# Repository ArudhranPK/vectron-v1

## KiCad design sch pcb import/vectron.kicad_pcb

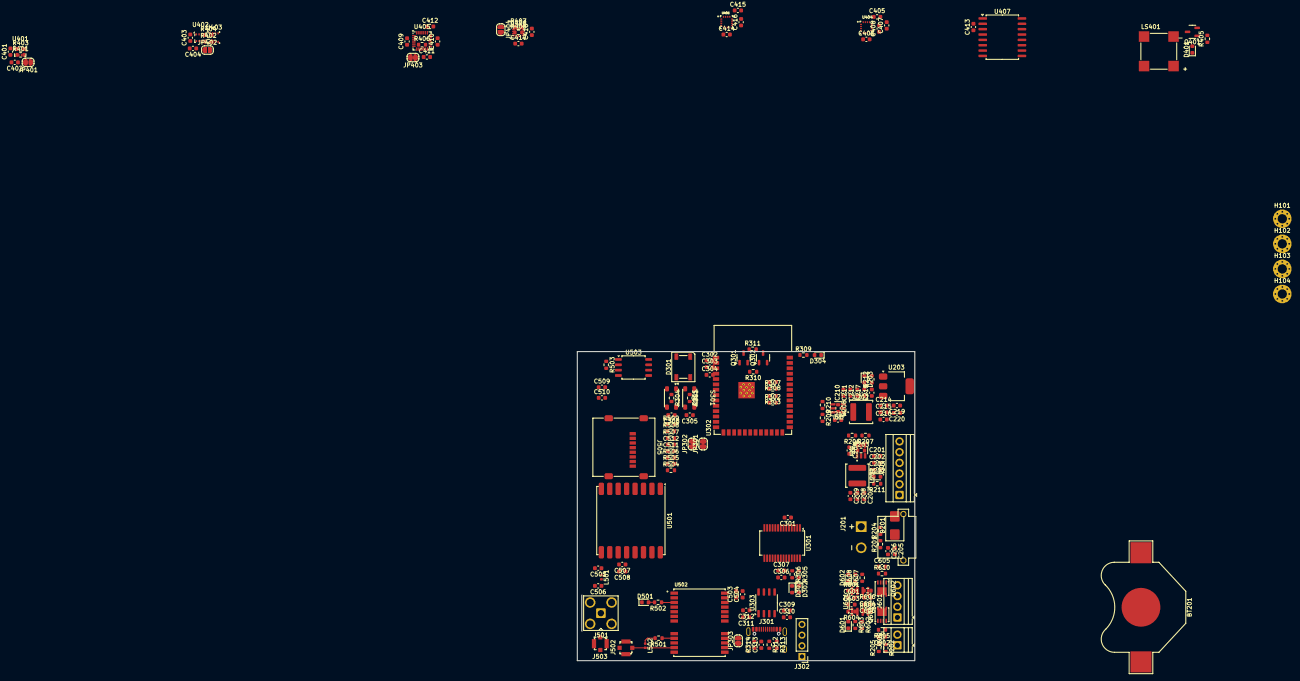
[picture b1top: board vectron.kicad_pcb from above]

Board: 4 copper layers, 80.1 x 73.3 mm, 183 parts (0 on the bottom side), 100 nets.

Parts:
BT201: BATT_3V; BatteryHolder_Multicomp_BC-2001_1x2032_modified
C201, C204, C206, C209, C210, C213, C216, C217, C220, C301, C304, C305, C307, C308, C310, C312, C313, C401, C402, C403, C404, C405, C406, C409, C410, C411, C413, C414, C415, C417, C418, C601, C602, C603, C604, C605, C606: 100nf; C_0603_1608Metric
C202, C203, C205, C211, C212, C218, C219, C302, C303, C306, C309, C311, C416, C503, C504, C507, C508, C509, C510, C511, C512: 10uf; C_0603_1608Metric
C207, C208, C214, C215: 22uf; C_0603_1608Metric
C407: 4u7f; C_0603_1608Metric
C408: 220nf; C_0603_1608Metric
C412: 2n2f; C_0603_1608Metric
C505, C506: 3pf; C_0603_1608Metric
D201: SS24-SMB; D_SMB
D202, D203: white; LED_0603_1608Metric
D301: WS2812B; LED_WS2812B_PLCC4_5.0x5.0mm_P3.2mm
D302, D303, D304: blue; LED_0603_1608Metric
D401: SS24-SMB; LED_0603_1608Metric
D501: green; LED_0603_1608Metric
D601, D602: red; LED_0603_1608Metric
H101, H102, H103, H104: MountingHole_Pad; MountingHole_2.2mm_M2_Pad_Via
J201: XT30PW-M; AMASS_XT30PW-M
J202: Screw_01x02; TerminalBlock_Xinya_XY308-2.54-2P_1x02_P2.54mm_Horizontal
J301: USB_C_Receptacle_USB2.0_16P; USB_C_Receptacle_GCT_USB4105-xx-A_16P_TopMnt_Horizontal
J302: Conn_01x04_Pin; PinHeader_1x04_P2.54mm_Vertical
J501: Conn_Coaxial; SMA_Amphenol_901-143_Horizontal
J502, J503: 0734120114; Molex_734120114_UMC_RF_CONN_Vertical
J504: Screw_Terminal_01x06; TerminalBlock_Xinya_XY308-2.54-6P_1x06_P2.54mm_Horizontal
J505: Micro_SD_Card; microSD_HC_Molex_47219-2001
J601: Screw_Terminal_01x04; TerminalBlock_Xinya_XY308-2.54-4P_1x04_P2.54mm_Horizontal
JP301, JP302, JP303, JP401, JP402, JP403, JP404: Jumper; SolderJumper-2_P1.3mm_Open_RoundedPad1.0x1.5mm
L201, L202: SWPA5040S3R3NT 3u3h; L_Sunlord_SWPA5040S
L501: 10nh; L_0402_1005Metric
L502: 27nh; L_0402_1005Metric
LS401: CMT-8530S-SMT; CUI_CMT-8530S-SMT
Q301, Q302, Q401: SS8050; SOT-23-3
Q601, Q602: SISA12ADN; Vishay_PowerPAK_1212-8_Single
R201, R202: 18k; R_0603_1608Metric
R203, R208, R302, R303: 4k7; R_0603_1608Metric
R204, R205, R207, R210, R301, R304, R310, R311, R401, R402, R403, R404, R406, R407, R408, R503, R504, R505, R506, R507, R508, R509: 10k; R_0603_1608Metric
R206: 54k9; R_0603_1608Metric
R209: 33k2; R_0603_1608Metric
R211, R212, R305, R306, R309, R405, R502, R601, R602, R603, R604, R605, R606, R607, R608, R609, R610: 1k; R_0603_1608Metric
R307, R308: 2k2; R_0603_1608Metric
R312, R313: 5k1; R_0603_1608Metric
R314: 100k; R_0603_1608Metric
R501: 10; R_0603_1608Metric
S301, S302: TK-066S; tact switch 3.4x2.5mm
U201, U202: TPS563201DDCR; SOT95P280X110-6N
U203: AMS1117-3.3; SOT-223-3_TabPin2
U301: FT232RL; SSOP-28_5.3x10.2mm_P0.65mm
U302: ESP32-S3-WROOM-1
U303: USB6B1RL; SO-8_3.9x4.9mm_P1.27mm
U401, U402: BMP280; Bosch_LGA-8_2x2.5mm_P0.65mm_ClockwisePinNumbering
U403: BME280; Bosch_LGA-8_2.5x2.5mm_P0.65mm_ClockwisePinNumbering
U404: HMC5883L-TR; XDCR_HMC5883L-TR
U405: MPU-6050; InvenSense_QFN-24_4x4mm_P0.5mm
U406: MMC5983MA; PQFN50P300X300X100-16N
U407: DS3231M; SOIC-16W_7.5x10.3mm_P1.27mm
U408: LSM6DSL; LGA-14_3x2.5mm_P0.5mm_LayoutBorder3x4y
U501: RFM98W-433S2; HOPERF_RFM9XW_SMD
U502: NEO-6M-GPS; XCVR_NEO-6M-GPS
U503: W25Q128JVS; SOIC-8_5.3x5.3mm_P1.27mm
U601: LM358; SOIC-8_3.9x4.9mm_P1.27mm

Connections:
+3V3: C214.1, C215.1, C216.1, C219.1, C220.1, C302.1, C303.1, C304.1, C401.1, C402.1, C403.1, C404.1, C405.1, C406.1, C409.1, C410.1, C413.2, C414.1, C415.1, C417.1, C418.1, C503.1, C504.1, C507.1, C508.1, C509.1, C510.1, C511.1, C512.1, D301.1 (VDD), D401.1 (K), J505.4 (VDD), JP401.2 (B), JP402.2 (B), JP403.2 (B), JP404.2 (B), L202.2, LS401.P, R209.2, R212.2, R301.1, R302.1, R303.2, R304.1, R307.1, R308.2, R401.2, R402.2, R407.2, R503.2, R504.2, R505.2, R506.2, R507.2, R508.2, R509.2, R601.2, R606.2, U203.2 (VO), U302.2 (3V3), U401.6 (VDDIO), U401.8 (VDD), U402.6 (VDDIO), U402.8 (VDD), U403.6 (VDDIO), U403.8 (VDD), U404.2 (VDD), U404.4 (S1), U404.13 (VDDIO), U405.8 (VLOGIC), U405.13 (VDD), U406.2 (VDD), U406.4 (~SPI_CS), U406.13 (VDDIO), U407.2 (VCC), U408.5 (VDDIO), U408.8 (VDD), U501.13 (3.3V), U502.23 (VCC), U503.3 (~WP/IO_{2}), U503.7 (~HOLD/~RESET/IO_{3}), U503.8 (VCC), U601.8 (V+)
+5V: C207.1, C208.1, C209.1, J504.1, J504.4, L201.2, R206.2, R211.2
+BATT: C201.1, C202.1, C203.1, C205.1, C206.1, C210.1, C211.1, C212.1, C217.1, C218.1, D201.1 (K), J201.P, R201.1, R203.1, R208.1, U201.3 (VIN), U202.3 (VIN), U203.3 (VI)
+PYRO_BAT: J202.2, J601.1, J601.3, R202.1
/ESP32/CC1: J301.A5 (CC1), R312.1
/ESP32/CC2: J301.B5 (CC2), R313.1
/ESP32/DTR_BASE: Q301.1 (B), R310.2
/ESP32/RTS_BASE: Q302.1 (B), R311.2
/ESP32/RXL: R306.1, U301.22 (CBUS1)
/ESP32/RXLED: D303.1 (K), R306.2
/ESP32/TXL: R305.1, U301.23 (CBUS0)
/ESP32/TXLED: D302.1 (K), R305.2
/ESP32/built_led: D304.2 (A), R309.2
/ESP32/shield: C313.1, J301.S1 (SHIELD), JP303.1 (A), R314.1
/power/3V3LED: D203.2 (A), R212.1
/power/5VLED: D202.2 (A), R211.1
/power/EN1: R203.2, U201.5 (EN)
/power/EN2: R208.2, U202.5 (EN)
/power/SW1: C204.2, L201.1, U201.2 (SW)
/power/SW2: C213.2, L202.1, U202.2 (SW)
/power/VBST1: C204.1, U201.6 (VBST)
/power/VBST2: C213.1, U202.6 (VBST)
/power/VFB1: R206.1, R207.2, U201.4 (VFB)
/power/VFB2: R209.1, R210.2, U202.4 (VFB)
/pyro/+opamp1: C601.1, R601.1, U601.3 (+)
/pyro/+opamp2: C604.1, R606.1, U601.5 (+)
/pyro/-opamp1: C603.1, R604.2, U601.2 (-)
/pyro/-opamp2: C606.1, R609.2, U601.6 (-)
/pyro/opled1: D601.2 (A), R603.2
/pyro/opled2: D602.2 (A), R608.2
/pyro/opout1: R602.1, R603.1, U601.1
/pyro/opout2: R607.1, R608.1, U601.7
/sensors1/BMP_CSB: R401.1, U401.2 (CSB)
/sensors1/BUZZER_BASE: Q401.1 (B), R405.2
/sensors1/BUZZER_NEGATIVE: D401.2 (A), LS401.N, Q401.3 (C)
/sensors1/CPOUT: C412.1, U405.20 (CPOUT)
/sensors1/HMC_C1: C407.1, U404.10 (C1)
/sensors1/MMC_CAP: C416.1, U406.10 (CAP)
/sensors1/REGOUT: C411.1, U405.10 (REGOUT)
/sensors2/dat1: J505.8 (DAT1), R504.1
/sensors2/dat2: J505.1 (DAT2), R509.1
/sensors2/gps_inductor: L502.1, R501.2
/sensors2/gps_led: D501.2 (A), R502.2
/sensors2/gps_pulse: R502.1, U502.3 (TIMEPULSE)
/sensors2/lora_ant_out: C506.1, J501.1 (In), J503.2, L501.2
BATT_RTC_GPS: BT201.1 (+), U407.14 (VBAT), U502.22 (V_BCKP)
BME_CSB: R402.1, U402.2 (CSB), U403.2 (CSB)
BME_SDO: JP402.1 (A), R404.1, U402.5 (SDO), U403.5 (SDO)
BMP_SDO: JP401.1 (A), R403.1, U401.5 (SDO)
BOOT: C308.1, Q302.3 (C), R304.2, S302.1, S302.2, U302.27 (IO0)
BUILT_IN_LED: R309.1, U302.38 (IO2)
BUZZER: R405.1, U302.31 (IO38)
CONTINUITY1: R602.2, U302.32 (IO39)
CONTINUITY2: R607.2, U302.33 (IO40)
DRAIN1: J601.2, Q601.5 (D), R604.1
DRAIN2: J601.4, Q602.5 (D), R609.1
DTR: Q302.2 (E), R310.1, U301.2 (DTR)
ENABLE: C305.1, Q301.3 (C), R301.2, S301.1, S301.2, U302.3 (EN)
ESP_USBD+: JP301.2 (B), U302.14 (USB_D+)
ESP_USBD-: JP302.2 (B), U302.13 (USB_D-)
FLASH_CS: R503.1, U302.8 (IO15), U503.1 (~CS)
GND: BT201.2 (-), C201.2, C202.2, C203.2, C205.2, C206.2, C207.2, C208.2, C209.2, C210.2, C211.2, C212.2, C214.2, C215.2, C216.2, C217.2, C218.2, C219.2, C220.2, C301.2, C302.2, C303.2, C304.2, C305.2, C306.2, C307.2, C308.2, C309.2, C310.2, C311.2, C312.2, C313.2, C401.2, C402.2, C403.2, C404.2, C405.2, C406.2, C407.2, C409.2, C410.2, C411.2, C412.2, C413.1, C414.2, C415.2, C416.2, C417.2, C418.2, C503.2, C504.2, C505.2, C506.2, C507.2, C508.2, C509.2, C510.2, C511.2, C512.2, C601.2, C602.2, C603.2, C604.2, C605.2, C606.2, D202.1 (K), D203.1 (K), D301.3 (VSS), D304.1 (K), D501.1 (K), D601.1 (K), D602.1 (K), H101.1, H102.1, H103.1, H104.1, J201.N, J202.1, J301.A1 (GND), J301.A12 (GND), J301.B1 (GND), J301.B12 (GND), J302.4, J501.2 (Ext), J502.1, J503.1, J504.2, J504.5, J505.6 (VSS), J505.9 (SHIELD), JP303.2 (B), Q401.2 (E), Q601.1 (S), Q601.2 (S), Q601.3 (S), Q602.1 (S), Q602.2 (S), Q602.3 (S), R204.2, R205.2, R207.1, R210.1, R312.2, R313.2, R314.2, R403.2, R404.2, R406.2, R408.2, R605.2, R610.2, S301.3, S301.4, S302.3, S302.4, U201.1 (GND), U202.1 (GND), U203.1 (GND), U301.7 (GND), U301.18 (GND), U301.21 (GND), U301.25 (AGND), U301.26 (TEST), U302.1 (GND), U302.40 (GND), U302.41 (GND), U303.4 (GND), U303.5 (GND), U401.1 (GND), U401.7 (GND), U402.1 (GND), U402.7 (GND), U403.1 (GND), U403.7 (GND), U404.9 (GND), U404.11 (GND), U405.1 (CLKIN), U405.11 (FSYNC), U405.18 (GND), U406.9 (GND), U406.11 (GND), U407.5 (GND), U407.6 (GND), U407.7 (GND), U407.8 (GND), U407.9 (GND), U407.10 (GND), U407.11 (GND), U407.12 (GND), U407.13 (GND), U408.2 (SDX), U408.3 (SCX), U408.6 (GND), U408.7 (GND), U501.1 (GND), U501.8 (GND), U501.10 (GND), U502.10 (GND), U502.12 (GND), U502.13 (GND), U502.24 (GND), U503.4 (GND), U601.4 (V-)
LORA_ANT: C505.1, L501.1, U501.9 (ANT)
LORA_CS: U302.22 (IO14), U501.5 (NSS)
LORA_DIO0: U302.17 (IO9), U501.14 (DIO0)
LORA_RST: U302.21 (IO13), U501.6 (RESET)
LSM_CS: R407.1, U408.12 (CS)
LSM_SAO: JP404.1 (A), R408.1, U408.1 (SDO/SA0)
MAIN_BAT: R201.2, R204.1, U302.23 (IO21)
MPU_AD0: JP403.1 (A), R406.1, U405.9 (AD0)
PROG_LED: D301.4 (DIN), U302.4 (IO4)
PYRO_BAT: R202.2, R205.1, U302.39 (IO1)
P_USBD+: JP301.1 (A), U301.15 (USBD+), U303.7 (D+OUT)
P_USBD-: JP302.1 (A), U301.16 (USBD-), U303.6 (D-OUT)
RF_IN: J502.2, L502.2, U502.11 (RF_IN)
RTS: Q301.2 (E), R311.1, U301.3 (RTS)
RXD0: U301.1 (TXD), U302.36 (RXD0)
RXD1: U302.11 (IO18), U502.20 (TXD1)
SCL1: R303.1, U302.7 (IO7), U401.4 (SCK), U404.1 (SCL), U405.23 (SCL), U407.16 (SCL)
SCL2: R308.1, U302.5 (IO5), U402.4 (SCK), U403.4 (SCK), U406.1 (SCL/SPI_SCK), U408.13 (SCL)
SDA1: R302.2, U302.12 (IO8), U401.3 (SDI), U404.16 (SDA), U405.24 (SDA), U407.15 (SDA)
SDA2: R307.2, U302.6 (IO6), U402.3 (SDI), U403.3 (SDI), U406.16 (SDA/SPI_SDI), U408.14 (SDA)
SD_CS: J505.2 (DAT3/CD), R508.1, U302.9 (IO16)
SERVO1: J504.3, U302.24 (IO47)
SERVO2: J504.6, U302.25 (IO48)
SETC: C408.2, U404.12 (SETC)
SETP: C408.1, U404.8 (SETP)
SPI_CLK: J505.5 (CLK), R506.1, U302.18 (IO10), U501.4 (SCK), U503.6 (CLK)
SPI_MISO: J505.7 (DAT0), R505.1, U302.20 (IO12), U501.2 (MISO), U503.2 (DO/IO_{1})
SPI_MOSI: J505.3 (CMD), R507.1, U302.19 (IO11), U501.3 (MOSI), U503.5 (DI/IO_{0})
TRIGGER1: C602.1, Q601.4 (G), R605.1, U302.34 (IO41)
TRIGGER2: C605.1, Q602.4 (G), R610.1, U302.35 (IO42)
TXD0: U301.5 (RXD), U302.37 (TXD0)
TXD1: U302.10 (IO17), U502.21 (RXD1)
USBD+: J301.A6 (D+), J301.B6 (D+), J302.1, U303.2 (D+IN)
USBD-: J301.A7 (D-), J301.B7 (D-), J302.2, U303.3 (D-IN)
VBUS: C309.1, C310.1, J301.A4 (VBUS), J301.A9 (VBUS), J301.B4 (VBUS), J301.B9 (VBUS), J302.3, U303.1 (V_IN)
VCCIO: C301.1, D302.2 (A), D303.2 (A), U301.4 (VCCIO), U301.17 (3V3OUT)
VCC_RF: R501.1, U502.8 (RSVD_8), U502.9 (VCC_RF)
VUSB: C306.1, C307.1, C311.1, C312.1, D201.2 (A), U301.20 (VCC), U303.8 (V_OUT)

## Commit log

2025-06-13 added servo and finished esp32 connections
2025-06-13 drawings generated
2025-06-13 rearranging for aesthetics
2025-06-13 minor changes
2025-07-19 uploaded new pdschematic pdf
